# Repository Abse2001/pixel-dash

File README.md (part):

# Pixel Dash

## Accepted populated handheld

The populated AM3354 handheld connects **37 of 50 DDR links** on drilled CAM. A3, A5 and A6 now fit the command placement window together. A joint CPU breakout also shortened WEn. Both complete data bytes, all 44 byte vias and both clock conductors match the locked geometry. The 36-link board remains available at 618d9c6. Fabrication remains on hold. [Full board, top copper](previews/accepted-handheld.png) · [Accepted board and electrical checks](production/accepted) · [Earlier A3/A5/A6 breakout](https://github.com/Abse2001/pixel-dash/tree/82bd23d/studies/paired-command-breakout/return-preserved)

LCD_D1 and LCD_D2 have continuous full-width adjacent ground from their SYSBOOT resistors to the panel outside the plated launches. LCD_D1 shortened from 89.121 to 86.448 mm with nine transitions instead of ten. LCD_D2 shortened from 93.848 to 93.075 mm and retains twelve transitions. Both CPU strap taps remain open. The export has 23 remaining raster ground-coverage findings. [Full-width raster check](production/accepted/raster-reference.txt) · [Physical endpoints](production/accepted/drilled-cam.txt)

Drilled CAM verifies the touch interrupt from AM3354 V14 to R_TOUCH_IRQ pin 1 and verifies pin 2 reaches the 3.3 V DCDC4 rail. Its CPU-side via clears the reference copper under LCD_D9. This closes one of the 39 previously split board nets. Touch SDA and SCL remain open. [Whole-board CAM report](production/accepted/drilled-cam.txt)

The SYSBOOT resistors now reach 16/16 panel data pins on drilled CAM. The new resistor-to-panel connections are bits 4, 5, 6 and 7. The CPU straps physically resolve to `01000?00???????1` (bits 15 through 0). The eight question marks identify unconnected CPU taps. The fitted bias word is 0x4017. Both byte lanes, CK/CKn and all prior command geometry match 740abbe. Full-width DDR/MMC0 checks pass, and the new panel conductors have full ground reference on the export. The LCD_D1 and LCD_D2 repairs reduced the original 25 raster reference findings to 23. [Exact physical strap and panel results](production/accepted/drilled-cam.txt) · [Raster reference](production/accepted/raster-reference.txt)

All previously passing command windows remain passing. A3, A5 and A6 measure 38.14850, 37.21347 and 36.67605 mm inside the 36.14999–38.68999 mm window. A9 shortened from 39.65733 to 38.60715 mm with its RAM-side via retained and the CPU-side transition moved. Its two L1–L4 transitions have 2.84 mm total contacted depth. Modeled arrival is 241.469 ps, or +4.999 ps to mean CK, with 0.08284 mm to the length ceiling. WEn shortened from 40.50792 to 38.66645 mm, leaving 0.02354 mm to the placement ceiling. It now has six transitions and 5.30 mm total contacted depth. The additional inner-layer routing increases modeled flight from 270.856 to 287.897 ps. The nominal first-arrival setup/hold requirement changes from 488.300/311.904 to 505.341/294.863 ps. The route preserves the L3 feed to the RAM supply via and all 20 selected byte return-path measurements. Two connected signals still miss the placement window. BA1 is 9.82286 mm long and CKE is 12.04368 mm short. The setup and hold calculations still need actual source launch and receiver margins. Thirteen signals remain open. [Per-net timing and spans](production/accepted/command-timing.csv) · [Physical open nets](production/accepted/ddr-power-lands.txt)

The separate 38-link study connects A0 while retaining the A9 and WEn placement passes and both locked data bytes. A0 is 51.05487 mm, 12.36488 mm above the placement ceiling. Drilled CAM verifies the extra connection. The study also records the A11/A14 and shorter A0/A7 corridor trials and the CKE and boot launch screens. [Study board, CAM and timing](https://github.com/Abse2001/pixel-dash/tree/b65d4f5/studies/a0-a9-paired)

The 37-link board has 78 signal transitions that change adjacent reference between L2 ground and L3 DDR supply. The longest geometric transfer is on D1 at (−59.455, 15.245) mm. The two vias of C_DDR40 are 9.4851 and 8.7965 mm away. The supply leg includes a staggered transition. Full-width copper coverage alone cannot establish the impedance of this loop. [Reference transfers](production/accepted/reference-transitions.csv)

The drilled copper also changes the distance a return can travel around slots. A 25 µm grid search on the accepted Gerbers finds a continuous L2 ground path of 10.3275 mm and an L3 supply path of 9.1970 mm from the D1 launch at (−59.455, 15.245) mm to the annuli of C_DDR40. An isolated central-bypass study shortens the corresponding paths to 4.7000 and 3.9039 mm. These are lengths of explicit paths in the connected copper. Return current spreads over the planes, and its distribution and transfer impedance remain open. For five selected byte signals, 18 of 20 legs have a path outside the launch region. Two land-side stubs terminate inside it. Run `python checks/measure-return-plane-path.py dist/index.circuit.json engineering.zip DDR_D1 DDR_D14 DDR_D9 DDR_D12 DDR_DQS0`. [Accepted path measurements](production/accepted/plane-paths.csv) · [Central-bypass layout and CAM](https://github.com/Abse2001/pixel-dash/tree/1a3a72e/studies/central-ddr-return) · [A11 escape and A14 restoration study](https://github.com/Abse2001/pixel-dash/tree/c827d16/studies/a11-escape)

For DDR3L-800, Micron's AC135/DC90 input requirements depend on both the command slew and the differential clock slew at the receiver. At 2.0 V/ns command and 1.0 V/ns clock, Table 62 adds 108 ps setup and 95 ps hold, the largest tabulated additions. Table 64 also requires 213 ps continuously beyond the AC threshold for that command slew. The report applies three tabulated slew pairs to each connected synchronous command and gives the required CPU valid interval. Measured or simulated edge shapes at both die loads, clock jitter and source launch timing are still required for margin. Run `python checks/command-receiver-corners.py production/accepted/command-timing.csv`. [Per-signal slew screens](production/accepted/receiver-slew.csv) · [Micron Tables 60–64](https://media.digikey.com/pdf/Data%20Sheets/Micron%20Technology%20Inc%20PDFs/MT41K_DDR3L_4Gb_Rev.Q_Dec2017_DS.pdf#page=102)

At DDR3L-800, a reflected-edge screen across the 13 routed synchronous commands gives a common source capture-phase window of 633.825–2031.463 ps at IOCTRL 0x273 and 687.219–2015.253 ps at reset IOCTRL 0x000. BA1 limits setup and BA0 limits hold in both scenarios. Phase is measured from one source command transition to the rising capture edge, assuming the next command transition occurs 2500 ps later. Each bound includes the worst of 16 terminal-load combinations, both edge polarities, and the maximum Table 62 setup and hold additions (108 and 95 ps) conditional on the input slews lying within the tabulated range. These are source timing requirements. Actual launch phase, slew, PVT, clock jitter, simultaneous switching and the two die responses still require qualification. Reproduce either report with `checks/command-source-echo.py` and `--launch-window --ioctrl 0x273` or `--launch-window --ioctrl 0`. [0x273 per-net bounds](production/accepted/capture-window-0x273.csv) · [Reset per-net bounds](production/accepted/capture-window-0.csv)

The modeled edge slopes limit how the capture-window results can be used. At IOCTRL 0x273 the differential clock is 5.385–6.740 V/ns and the nominal command setup slope is 2.355–3.244 V/ns. All 416 modeled pin/load/polarity cases fall outside Micron Table 62's 1–4 V/ns clock and 0.4–2 V/ns command grid for setup. At reset IOCTRL 0, 208 of 416 cases have both nominal setup slopes in range. All modeled hold edges at both settings cross earlier than the nominal DC-to-VREF secant within that interval and require Micron’s tangent construction. The earlier conditional capture windows cannot establish receiver margin. The edge screen uses the ±180 mV differential thresholds in Table 26, VREF to AC135 for command setup and DC90 to VREF for hold. It uses the reflected single-edge model at the two-die package terminals. Actual source launch, per-die waveforms, impedance and jitter are still open. Reproduce with `checks/command-source-echo.py` using the same circuit, timing CSV and TI archive and the `--slew-screen` option. [0x273 edge results](production/accepted/edge-slew-0x273.csv) · [Reset edge results](production/accepted/edge-slew-0.csv) · [Micron Tables 26, 31 and 62](https://media.digikey.com/pdf/Data%20Sheets/Micron%20Technology%20Inc%20PDFs/MT41K_DDR3L_4Gb_Rev.Q_Dec2017_DS.pdf)

The first-arrival study uses the nominal rising and falling 50 Ω fixture waveforms in TI ZCZ IBIS Model_364. The study assumes the SR10 and I011 command and clock settings in the three DDR_CMDx_IOCTRL registers (low ten bits 0x273), the fitted 49.9 Ω VTP resistor and 1.35 V. These are simulation inputs. Boot firmware/readback still needs to establish what the controller drives. TI TRM Table 9-9 puts A3 and A5 in CMD0, A11 in CMD1 and A14 in CMD2. The model checks all 28 command/control/clock CPU ball names against the IBIS selector.

For each routed synchronous command, the study propagates the incident waveform through its measured board flight and a 50 Ω lossless line into the Micron Table 7 terminal capacitance. It evaluates rising and falling data against a rising differential CK at the 16 vertices of the jointly specified CK, CKn and command load region. Capacitance is the package-terminal value, counted once. The reported intervals refer to the 50% swing of each fixture edge with zero relative source launch offset. They include the AC135 setup and DC90 hold threshold crossings and use the reference-slew receiver requirements. A negative pre-echo headroom marks a crossing beyond the first incident wave's causal range. The result excludes source/package discontinuities, reflections from prior cycles, bit-pattern coupling, slew derating, AC dwell and PVT/jitter. It cannot establish either die's setup or hold margin. Reproduce with `python checks/command-first-arrival.py dist/index.circuit.json production/accepted/command-timing.csv sprm552c.zip` using TI's original ZIP. [Per-command first arrivals](production/accepted/first-arrival.csv) · [TI ZCZ IBIS archive](https://www.ti.com/lit/zip/SPRM552) · [TI AM335x TRM, §9.2.5](https://www.ti.com/lit/pdf/spruh73) · [Micron TwinDie Table 7](https://datasheet.lcsc.com/datasheet/pdf/1a552aaada9c9cb5685b5fb937531c2e.pdf)

The BA0 and CKE control study includes repeated source and capacitive-load reflections. It fits a time-dependent linear source reflection coefficient to the two complementary TI 50 Ω V/T fixture waveforms on their supplied time axes. CK and CKn propagate separately to the differential crossing. At DDR3L-800, the nominal 0x273 case requires up to 426.667 ps setup and 373.537 ps hold for BA0, and 432.274 ps setup and 367.930 ps hold for CKE at reference slew. Across the 32 sampled cases per net, the largest change in setup from including echoes is 0.013 ps for BA0 and 0.004 ps for CKE. Changing the driver assumption has a much larger effect.

TI TRM Table 9-9 maps BA0 to CMD0 pin 2, CK/CKn to CMD0 pins 4/5, and CKE to CMD2 pin 0. The command IOCTRL registers reset to zero. Under this setting the tables specify the fastest slew and 1.6 × Rext, represented here by nominal Model_370. That sensitivity case requires up to 480.236/389.747 ps setup/hold for BA0 and 485.668/384.140 ps for CKE. Boot firmware or register readback must establish the actual values at initialization. Micron Table 7 explicitly includes BA0 and CKE in the package-terminal load limits. The synchronous CKE screen covers power-down entry/exit and self-refresh entry. Self-refresh exit has separate asynchronous requirements. Both simulations assume an isolated edge, a 50 Ω lossless line, zero package-delay imbalance, nominal IBIS waveforms and reference slew. Actual controller launch, package topology, coupling, jitter, voltage/temperature corners and operating-mode sequencing remain open. Run `python checks/command-source-echo.py dist/index.circuit.json production/accepted/command-timing.csv sprm552c.zip --ioctrl 0x273` and repeat with `--ioctrl 0`. [0x273 corner results](production/accepted/source-echo.csv) · [Reset-setting sensitivity](production/accepted/source-echo-reset.csv) · [TI AM335x TRM](https://www.ti.com/lit/ug/spruh73q/spruh73q.pdf)

At the modeled receiver, all isolated BA0, CKE and WEn edges remain beyond the Micron AC135 input threshold through the simulation end. Across 96 load/polarity cases per drive setting the shortest observed continuous dwell is 1,466.596 ps at 0x273 and 1,348.351 ps at 0x000. Micron Table 64 requires up to 213 ps at DDR3L-800. These are lower bounds on isolated-edge dwell. Successive commands, prior reflections and actual launch still govern receiver margin. Reproduce with the source-echo command above and `--dwell`. [0x273 dwell](production/accepted/receiver-dwell.csv) · [0x000 dwell](production/accepted/receiver-dwell-reset.csv) · [Micron Table 64](https://media.digikey.com/pdf/Data%20Sheets/Micron%20Technology%20Inc%20PDFs/MT41K_DDR3L_4Gb_Rev.Q_Dec2017_DS.pdf#page=104)

WEn is CMD0 pin 1. Its reflected-edge calculation over 32 load and polarity cases requires source setup/hold of 505.341/294.863 ps at IOCTRL 0x273 and 558.735/311.073 ps at IOCTRL 0x000. At a 2,500 ps period with one command change per cycle, the capture edge would need to follow the source change by 505.341–2,205.137 ps or 558.735–2,188.927 ps respectively, before slew derating, launch variation, coupling and jitter. These intervals express source requirements. TI datasheet Table 7-58 specifies DDR clock period and supplies no pin-level command launch extrema. [TI AM335x datasheet, §7.7.2.3.1](https://www.ti.com/lit/ds/symlink/am3354.pdf)

TI TRM §7.3.6 identifies the PHY registers as write-only owing to a silicon bug. Record the executed SPL writes for CMD0/1/2 slave ratios at 0x44E1201C, 0x44E12050 and 0x44E12084, and clock inversion at 0x44E1202C, 0x44E12060 and 0x44E12094. The ratio unit is one clock period divided by 256 (9.766 ps at 400 MHz). Table 7-260 and the slave-ratio field figure give differing reset values. Capture the programmed values and clock period before interpreting a ratio. Timing closure also needs characterized or measured command-to-CK launch extrema for the operating configuration. [TI AM335x TRM, Tables 7-260, 7-261 and 7-263](https://www.ti.com/lit/ug/spruh73q/spruh73q.pdf)

Read CONTROL_STATUS at 0x44E10040 after a power-on reset with the panel attached and again with it disconnected. The PWRONRSTn rising edge latches SYSBOOT. A warm reset retains the prior sample. Validate the saved register word with `python checks/check-sysboot.py dist/index.circuit.json --control-status VALUE`. The decoder combines register bits 23:16 and 7:0 into the sixteen strap bits and compares them to the fitted 0x4017 intent. A physical cold-boot capture is pending. [TI TRM Table 9-14 and §26.1.5.2](https://www.ti.com/lit/ug/spruh73q/spruh73q.pdf)

For cold bring-up, capture the three command IOCTRL registers, VTP_CTRL and DDR_CKE_CTRL before the first external memory access. TI TRM Table 9-63 gives VTP_CTRL bits 6 and 5 as dynamic compensation enable and training complete. Table 9-86 gives DDR_CKE_CTRL bit 0 as the gate on the PHY’s CKE output. Its reset value holds external CKE low, which prevents the memory from registering commands. The zero-IOCTRL sensitivity calculation assumes a calibrated driver operating after the gate opens. The power-on reset state itself cannot establish a receiver timing margin.

The fitted TwinDie datasheet delegates initialization to the 4 Gb monolithic device. Verify stable power with RESET# low for at least 200 µs, CKE low for at least 10 ns before RESET# rises, and CKE low for the following 500 µs minus one clock. Before the first registered CKE high, verify valid CK for at least 10 ns and at least five clocks, plus ODT low for the required setup. At DDR3L-800 five clocks take 12.5 ns. RESET# remains physically open on the accepted board. Capture these signals on the first article alongside the supply ramp and retain the MMC0 cold-boot results with the panel attached and disconnected. [TI TRM Tables 9-63 and 9-86](https://www.ti.com/lit/ug/spruh73q/spruh73q.pdf) · [Micron DDR3L initialization](https://media.digikey.com/pdf/Data%20Sheets/Micron%20Technology%20Inc%20PDFs/MT41K_DDR3L_4Gb_Rev.Q_Dec2017_DS.pdf)

Run `bun run build` to materialize the exact qualified circuit at `dist/index.circuit.json`. To screen a reroute, run `bun run check:bytes path/to/candidate.circuit.json` with Python 3 and Shapely 2 installed. Both complete lanes must pass on the same populated candidate. Rerun drilled endpoint and short checks, full-width references, copper and via-edge clearance, drill spacing and supply connectivity on its own export before updating the pinned board. Placement ceilings and modeled flight are project screens. Hardware timing signoff remains open.

To repeat the populated DDR reference check, pass the same circuit and Gerber export to the checker. The thirteen open names must match exactly. Omit the open list for the complete 50-link gate.

```sh
python checks/audit-ddr-reference-planes.py dist/index.circuit.json --gerbers engineering.zip --full-width --study-open DDR_A0 DDR_A1 DDR_A10 DDR_A11 DDR_A12 DDR_A13 DDR_A2 DDR_A4 DDR_CASn DDR_CSn0 DDR_ODT DDR_RASn DDR_RESETn
```

The gate rejected the 45-link powered board for missing D1, D10 and D11. It also rejected the fully connected raster fallback on data and mask timing in both lanes. The accepted board has zero 0.102 mm copper, 0.1524 mm via-edge, drill-spacing or routed DDR reference findings. Thirty-nine whole-board nets still have disconnected copper. [All 22 timing results](production/accepted/byte-timing.csv) · [Drilled CAM](production/accepted/drilled-cam.txt) · [Full-width reference](production/accepted/ddr-reference.txt)

BA0 increased from 35.53782 to 36.26684 mm inside the 36.14999–38.68999 mm placement window. It remains on L1 with zero vias. Estimated flight is 209.223 ps, or −27.247 ps relative to mean CK, previously −31.452 ps. All 22 byte routes and both clock routes retain their fingerprints. Drilled CAM joins N5/P5 to DCDC4, all seven CPU DDR lands to the switched output, all eighteen DRAM supply lands to the DCDC3 inductor output, all 21 DRAM returns to ground, and both terminals of all 40 DDR capacitors to their intended domains. This proves copper continuity. Hot-load transient and receiver timing signoff remain open. MMC0 DAT3 and card detect now avoid the raster strap relief. DAT2 crosses it on L1, with a 0.5 mm return-via distance at each transition. The export has zero full-width MMC0 reference findings and retains all seven card signals and sequenced card power. [MMC0 return check](production/accepted/mmc0-reference.txt) [Power by land](production/accepted/ddr-power-lands.txt) · [Command and clock timing](production/accepted/command-timing.csv)

The command timing CSV gives the required valid interval at the AM3354 balls for the reference-slew DDR3L-800 screen. For board flight difference Δ = signal arrival − mean CK arrival, the required source setup is 365 + Δ ps and hold is 285 − Δ ps. BA0 requires 337.753 ps setup and 312.247 ps hold. The fitted TwinDie package has two command/clock loads. Controller launch limits, package loading, slew derating, clock jitter and stack tolerances are still needed for receiver margin. RESETn needs a sequencing check. Recompute with `python checks/measure-command-timing.py dist/index.circuit.json <prior-circuit.json>`. [Micron x8 device timing, Tables 60–64](https://media.digikey.com/pdf/Data%20Sheets/Micron%20Technology%20Inc%20PDFs/MT41K_DDR3L_4Gb_Rev.Q_Dec2017_DS.pdf#page=102) · [AM3354 DDR3 clock and PCB rules](https://www.ti.com/lit/ds/symlink/am3354.pdf)

At the current package coordinates, an in-memory comparison changes the 42 through vias inside the CPU or DRAM body to 18 mil lands and 10 mil holes. It produces 52 via-edge clearance findings and two drill-spacing findings. The blind and buried vias retain their actual drill spans in this comparison. TI Table 7-62 note 5 describes the 18 mil land for the minimum-layer-count via-channel escape. Qualification of the installed four-layer HDI launches remains open. [Escape measurements](production/accepted/escape-lands.txt)

The reference copper fills the obsolete antipads of the two removed VREFCA bypass vias. Relative to the accepted MMC0 board the L2 ground plane regains 0.66515 mm² and L3 DDR supply regains 0.66893 mm². Full-width checks on the 37 routed DDR signals and seven MMC0 signals remain clean. The conservative whole DDR envelope still has 57 findings. Outside nominal via antipads, L2 ground coverage misses 12.38295 mm² and L3 DDR supply coverage misses 91.82907 mm². Existing inner traces and the neighboring ground pour account for most of the residual. The separate raster check reproduces the fallback’s 25 findings on 14 routed signals. [Whole-envelope CAM](production/accepted/ddr-envelope.txt)

An earlier 37-link study added A10 to the 36-link fallback. A7, A10 and A14 fit the nominal command length window together. A6 reaches both balls but exceeds its ceiling by 11.45448 mm, so the accepted build retains the shorter A6. The drilled study has 13 DDR opens and both bytes pass unchanged. [Study PCB, clock-relative timing and drilled endpoints](https://github.com/Abse2001/pixel-dash/tree/8df6773/studies/accepted-a10-corridor/37-links)

To verify an intermediate export, pass its native circuit, its Gerber/Excellon ZIP and the independently expected open control names to `python checks/audit-cam-connectivity.py BOARD ZIP --ddr-checkpoint OPEN_CONTROL ...`. This checks exactly which physical DDR pairs connect, rejects aliases and shorts, requires all data, masks, strobes and clocks, and verifies DDR power lands and MMC0. The normal whole-board invocation still requires all 50 DDR pairs. Run the separate timing and reference checks on the same circuit and export.

## Separate powered routing studies

Powered checkpoint `7ac53c5` connects LCD data-enable from U1.R6 to J_LCD pin 9 with a continuous full-width reference. Drilled CAM verifies 12/29 CPU-to-panel signals, 16/16 panel-side strap taps, seven CPU strap states and 45/50 DDR links. Twenty-eight mapped board nets remain split. DE's nominal flight is 0.7635 ns later than PCLK. Panel receiver timing remains open. All 71 local DDR returns, sequenced MMC0, the DDR timing CSV, copper, via-edge and drill checks retain their prior results. [Full PCB](https://github.com/Abse2001/pixel-dash/blob/7ac53c5/studies/powered-cpu-io/powered-panel-taps.png) · [Drilled CAM](https://github.com/Abse2001/pixel-dash/blob/7ac53c5/studies/powered-cpu-io/panel-DE-cam.txt) · [Raster flight](https://github.com/Abse2001/pixel-dash/blob/7ac53c5/studies/powered-cpu-io/panel-clock-flight.csv)

West trial `a466259` restores D0 alongside D5, D7, DQM0 and both shortened strobes. The six fit the 20.6001 mm placement cap, TI matching limits and the nominal ±3.6633 ps board-skew screen together. The new strobe mismatch is 0.0260 mm against 0.127 mm. Drilled CAM verifies 40/50 links. All routed traces and the DDR envelope pass reference checks. The separate copper, 6 mil via-edge, drill spacing and nonlocal DDR contact audits report zero findings. Fifteen more command/address paths fit the 30.150–32.690 mm placement window. A3, A6, A11 and CKE still miss it. Five byte-zero DQ paths and the full receiver timing budget remain open. The powered and fully connected fallbacks remain available. Fabrication is on hold. [Per-net pass/fail with targets and residuals](https://github.com/Abse2001/pixel-dash/blob/2e49c6f/studies/powered-ddr3l-offset/short-strobe/west-gate-status.csv) · [D2 physical trial](https://github.com/Abse2001/pixel-dash/tree/study/powered-ddr3l-offset/studies/powered-ddr3l-offset/short-strobe/escape-screen) · [Physical geometry, pin map and receiver assumptions](https://github.com/Abse2001/pixel-dash/tree/a466259/studies/powered-ddr3l-offset/short-strobe) · [Earlier B5 and command trials](https://github.com/Abse2001/pixel-dash/tree/01116f0/studies/powered-ddr3l-offset/rtc-reset)

The four-route west trial preserves the 20.600104 mm cap with both byte lanes installed. Local D12/D14 changes reduced the 0.102 mm copper findings from 25 to 24, the 6 mil via-edge findings from nine to eight and the full-width return findings from seven to six. Drilled CAM still finds shorts on the trial. The separate clean CKE study shortens CKE from 34.9054 to 34.8683 mm with 40 distinct links and all 71 local returns. Its 32.690 mm upper target and receiver timing remain open. [Four-route mapping, full circuit and physical findings](https://github.com/Abse2001/pixel-dash/tree/dd87640/studies/powered-ddr3l-offset/short-strobe/four-route-recheck) · [CKE timing and drilled CAM](https://github.com/Abse2001/pixel-dash/tree/4dfb0ab/studies/powered-ddr3l-offset/short-strobe/cke)

## Separate 50-link routing study

The complete candidate at 4b3d1c5 connects the handheld IRQ pull-up, keeps the 50 DDR routes and their vias identical to a4a71e2 and reduces the whole-board split-net count from 35 to 34. Drilled CAM explicitly verifies J3/VTP, RAM ZQ, the CPU and RAM VREF networks, divider rails, local bypass returns and their mutual isolation. [Complete candidate and physical land groups](https://github.com/Abse2001/pixel-dash/blob/4b3d1c5/checks/current-touch-irq-cam.txt)

The powered board at 408d38c connects touch IRQ, the panel-side D3 and D4 strap taps, and the complete U1.T4 to LCD D7 path. Exact CAM shows 45 distinct DDR signals, 13/16 panel taps, 8/29 CPU-to-panel signals, seven physically resolved CPU straps, and 34 split mapped nets. Timing is unchanged from d8461d7. N5/P5, VTP, ground and full-width return checks pass. The original 45-link d8461d7, 50-link 4b3d1c5 and rotated b0317c2 stay separate. [Full powered PCB and CAM](https://github.com/Abse2001/pixel-dash/tree/408d38c/studies/powered-cpu-io) · [Byte-zero simultaneous landing and installed-peer bounds](https://github.com/Abse2001/pixel-dash/tree/study/byte0-two-transition/studies/byte0-two-transition)

The rotated study at b0317c2 connects U1.V14 to the touch IRQ pull-up and preserves all mapped handheld ground connections. Fifty mapped whole-board nets remain split. The powered 45-link baseline stays at d8461d7. The 26-link study passes relative matching for its eight routed data lines, but all four routed upper-byte data lines and both upper strobes exceed the 14.200 mm project length gate. No in-byte remap alone can raise it beyond 14.99986 mm at this placement. [Full PCB snapshot and CAM](https://github.com/Abse2001/pixel-dash/tree/b0317c2/studies/quarter-turn/touch-irq) · [Per-net gate and remap bounds](https://github.com/Abse2001/pixel-dash/blob/b0317c2/studies/quarter-turn/d1-restored/remap-length-bound.csv)

The rotated study at b5e1c20 physically connects B5 (RTC reset) to PMIC PGOOD_BU, C5 to wake, and B4 to the 1.8 V D7/DCDC6 rail. B4 remains isolated from D6/DCDC5. All mapped ground lands and barrels join the UART ground probe, including the two nearby bypass returns. Twenty-six DDR signals, eight physical SYSBOOT straps, 22 CPU DDR bypasses, 14 DRAM bypasses and 71 local reference terminals pass their connectivity checks. The export still has 51 split mapped nets. [Full PCB snapshot, drilled CAM and timing](https://github.com/Abse2001/pixel-dash/tree/b5e1c20/studies/quarter-turn/rtc-reset)

The rotated populated study at 5494ca2 now connects 26 DDR signals. D1, D2, D3, D4, D10, D11, D12 and D14 pass present-peer and strobe matching plus the reference-stack delay screen together. All 71 local return terminals and both CPU supply feeds pass. Twenty-four DDR signals and whole-board closure remain open. [Full PCB snapshot, per-net limits and physical CAM](https://github.com/Abse2001/pixel-dash/tree/5494ca2/studies/quarter-turn/d1-restored)

The rotated RAM study at 9c71554 connects 25 distinct DDR signals on the powered handheld. D2/D3/D4 and D10/D11/D12/D14 pass their local TI length and modeled skew screens together. A10, A14, BA2 and CK/CKn are physically connected, with command timing still open. SYSBOOT0 reaches the CPU, its high strap and panel. All 71 local DDR return terminals pass. The powered 45-link baseline remains separate. [Full-board copper, per-net timing and drilled CAM](https://github.com/Abse2001/pixel-dash/tree/9c71554/studies/quarter-turn/ba2-breakout)

A separate 90° RAM placement at f7b27e7 routes D2, D3 and D4 together with a matched DQS0 pair. All five use two full-depth transitions, pass drilled CAM, and retain the local power and return paths. Worst modeled data skew is +1.7561 ps against ±3.6633 ps. This five-link study reserves startup space at SYSBOOT0. The unchanged RAM orientation leaves the entire SYSBOOT0 pad inside the required margin even if all DDR routes are lifted. [Timing, geometry, assembled study and drilled CAM](https://github.com/Abse2001/pixel-dash/tree/f7b27e7/studies/quarter-turn/timed-d234) · [Placement measurements](https://github.com/Abse2001/pixel-dash/tree/fcbf70b/studies/quarter-turn)

The powered board at d8461d7 also connects SYSBOOT7 and SYSBOOT12 to their bias resistors. Seven straps have verified physical states. The DDR bus remains at 45/50, with its full timing CSV and reference checks preserved. [Current powered board and drilled strap results](https://github.com/Abse2001/pixel-dash/tree/d8461d7/studies/powered-cpu-io)

The powered I/O checkpoint at 8c7bccf closes physical SYSBOOT10, panel D10, backlight PWM and amplifier logic bias. It retains the 45 DDR links, their complete timing CSV and the two power feeds. CAM reports 36 split whole-board nets. On the unchanged e5fd49f copper, the independent two-transition screen finds all nine D2/D3/D4 pin assignments disconnected within 20.4313 mm with their neighbors fixed. Releasing D0 or A1 restores individual reachability. [Powered I/O checkpoint and CAM](https://github.com/Abse2001/pixel-dash/tree/8c7bccf/studies/powered-cpu-io) · [Length-bounded topology screen](https://github.com/Abse2001/pixel-dash/tree/aa53c0e/studies/byte0-two-transition)

The powered baseline at 4fd6b86 shortens D5 to 25.7789 mm and retains its 45 distinct DDR links. On the alternative D15-passing branch, e5fd49f also removes two D7 transitions. D7 improves from +38.5076 to +16.5431 ps against the ±3.6633 ps model screen. Neither byte is complete. [Powered baseline timing](https://github.com/Abse2001/pixel-dash/blob/4fd6b86/studies/powered-byte1/d5-timing.csv) · [Alternative D5/D7 report and CAM](https://github.com/Abse2001/pixel-dash/tree/e5fd49f/studies/powered-byte1)

The native build of the powered 45-link board is verified at fc8c13c. A separate crossing trial at 354eaf8 brings D15 to 22.6549 mm with −1.8131 ps worst signed skew against the ±3.6633 ps model gate. It preserves the physical supplies and all 45 links, but moving the intermediate D3 bridge increases its skew to +54.1593 ps. Both byte lanes still have open signals. [Passing D15, D3 regression and exact CAM results](https://github.com/Abse2001/pixel-dash/tree/354eaf8/studies/powered-byte1)

The powered byte-1 study at 178dd63 has 45/50 distinct DDR connections. D12, D13 and D14 meet their TI strobe matching and model skew gates. D13 has just 0.0977 ps of modeled headroom. D15 is connected and retains full reference coverage, but its +5.4050 ps worst modeled skew exceeds the ±3.6633 ps screen. A10, A14, D1, D10 and D11 still need copper. Both N5/P5 and the VTP resistor return pass drilled CAM. [Timing, exact physical lands and intermediate fallbacks](https://github.com/Abse2001/pixel-dash/tree/178dd63/studies/powered-byte1)

The separate four-route breakout moves the switched DDR feed to make room for N5/P5. It physically connects 21/21 DCDC4 lands and 7/7 switched CPU DDR lands, with D1, D12, A10 and A14 lifted. [Boot-power study and screening results](https://github.com/Abse2001/pixel-dash/tree/ff755ca/studies/boot-ddr-breakout)

The four-layer AM3354 handheld at a4a71e2 retains 50 distinct CPU-to-RAM signals. BA2 shortened from 29.7914 to 28.6872 mm inside its 28.550–31.090 mm project window. Modeled arrival relative to mean CK improved from +10.7705 to +4.4005 ps. All DDR vias and the other 49 routes are unchanged. D11 and D15 now have continuous exported raster reference, including the strap traces. Independent CAM passes the common DDR envelope and full-width DDR, MMC0 and raster checks. Data-byte timing, command receiver signoff, N5/P5 power, physical straps and whole-board release remain open. [Full PCB snapshot](https://github.com/Abse2001/pixel-dash/blob/a4a71e2/previews/handheld.png) · [Per-net timing](https://github.com/Abse2001/pixel-dash/blob/a4a71e2/checks/current-ddr-change.csv) · [Physical land report](https://github.com/Abse2001/pixel-dash/blob/a4a71e2/checks/current-raster-taps-cam.txt)

The isolated D12/D1 trial retains all 50 distinct DDR pairs and passes copper, drilling and full-width reference checks. Both shortened signals still miss the TI and model matching targets. On the full board, A10/A14 also bound the N5/P5 escape. With D12/D1 entirely removed, neither supply pad has any exposed copper beyond the DDR margin. [Trial, timing targets and physical lands](https://github.com/Abse2001/pixel-dash/tree/12332c9/studies/d12-d1-breakout)

The separate boot study connects all 21 DCDC4 lands and SYSBOOT12. Its N5 and P5 copper and the V2 strap escape fail the common keepout. Both power pads are wholly inside even the smaller envelope defined by the locked bytes and clock. [Boot study and CAM findings](https://github.com/Abse2001/pixel-dash/tree/8c27acf/studies/complete-boot-escape)

The protected populated board has 36/50 distinct CPU–RAM signals and all 22 original byte routes. A8 measures 36.533 mm in its 36.150–38.690 mm placement window and arrives an estimated 0.107 ps before mean CK. RTC reset, wake, power hold and the isolated DCDC5/DCDC6 core and I/O connections pass drilled CAM. Six of sixteen SYSBOOT bits reach the CPU. [Protected board and timing](https://github.com/Abse2001/pixel-dash/tree/076b815/studies/clock-first) · [Protected full-board snapshot](https://github.com/Abse2001/pixel-dash/blob/076b815/studies/clock-first/populated-handheld.png)

The populated CPU escape trial connects the driven VREF divider and bypass to J4, J3 to the grounded calibration resistor, and all 21 CPU DCDC4 lands including N5/P5. Eight reset straps reach the CPU. Raster D12 reaches panel pin 15. Panel D3 reaches its strap resistor and still needs CPU ball R4. Twelve of sixteen panel data pins reach the strap pads, with 25 existing raster reference findings. Exported CAM resolves 36/50 distinct DDR pairs. A0 and A10 lost connectivity during clock routing, with identical CPU and DRAM pin assignments at both checkpoints. The 22 byte routes and clock pair retain the e4c906f geometry. Fourteen open DDR links, receiver timing and remaining boot and board-level checks keep fabrication on hold. [Physical evidence](https://github.com/Abse2001/pixel-dash/tree/b5356e7/studies/electrical-closure) · [Full-board PCB](https://github.com/Abse2001/pixel-dash/blob/b5356e7/studies/j4-vref/populated-handheld.png) · [Rejected A7/A10 exchange and exact CAM results](https://github.com/Abse2001/pixel-dash/tree/470c8be/studies/a7-a10-corridor)

## Populated handheld DDR data checkpoint

The tagged populated layout preserves all 22 passing byte 0 and byte 1 routes through 44 plated vias. The handheld Gerbers verify each distinct CPU-to-RAM pair, full-width reference coverage and zero mapped-land shorts. All 236 component courtyards clear after relocating eight passives. The other 28 DDR links remain open on this checkpoint. [Saved populated circuit and checks](https://github.com/Abse2001/pixel-dash/tree/pixel-dash-populated-ddr-locked/studies/data-bytes) · [Preserved breakout](https://github.com/Abse2001/pixel-dash/tree/pixel-dash-ddr-bytes-verified-2dc2af8)

## DDR timing study

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
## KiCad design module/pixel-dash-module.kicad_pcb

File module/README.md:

# AM3354 + DDR3L compute module

A 50 x 36 mm, 6-layer, 1.0 mm board that carries only what needs six layers: the AM3354BZCZD80 (U1), the
MT41K512M16VRP DDR3L (U_DDR), the DDR3 routing between them, their decoupling, the DDR reference/calibration
parts and the 24 MHz crystal. Everything else (power chip, boot straps, SD, USB, display, buttons, debug) lives on
the handheld and reaches the module through two Hirose DF40C-100DS-0.4V connectors (J1, J2, bottom side; the
handheld carries DF40C-100DP, LCSC C531031).

| Layer | Use |
|---|---|
| L1 top | DDR + handheld signals, both BGAs, crystal |
| L2 | ground |
| L3 | VDDS_DDR (west, the processor's north and south rows and its core-ball interior, with the DDR_VREF link embedded), 3V3 (the processor's middle rows and the east edge) |
| L4 | VDD_CORE, VDD_MPU, part of 1V8, DDR_VREF (between the chips), the 23 handheld signals whose balls sit inside the DDR fan-out |
| L5 | ground |
| L6 bottom | DDR + handheld signals, decoupling, connectors |

Through vias only, no blind or buried vias: 0.1 mm holes in 0.3 mm pads, via-in-pad throughout. The 0.1 mm hole keeps every hole wall at least 0.2 mm from other copper on the outer layers and 0.225 mm on the planes (JLCPCB: 0.2 mm); it needs a board of 1 mm or less with ENIG.

## What the handheld has to provide

Rails, through the connector pins listed in `fab/pinmap.csv`:

| Rail | Pins | Notes |
|---|---|---|
| VDD_CORE 1.1 V | J2, 4 | |
| VDD_MPU 1.1-1.26 V | J2, 6 | |
| VDDS_DDR 1.35 V (1.5 V) | J1, 4 | feeds the processor's DDR I/O, the memory and the VREF divider |
| VDD_3V3 | J1, 3 | VDDSHVx and USB 3.3 V |
| VDD_1V8 | J1, 2 | VDDS, PLL, oscillator, USB and ADC 1.8 V balls (ADC unused: VREFP on 1.8 V, VREFN on ground) |
| VDDS_RTC 1.8 V | J2, 1 | RTC domain; the internal RTC regulator is enabled (RTC_KALDO_ENn grounded, 1 uF on CAP_VDD_RTC) |
| GND | 55 | |

Follow the AM335x power-up sequence on the handheld (SPRS717L section 6.1) and drive `PWRONRSTn` and
`RTC_PWRONRSTn` from it. `LCD_D0..LCD_D15` are the SYSBOOT pins: the boot-mode resistors go on the handheld.
I2C0 needs its pull-ups there too. 75 signals are wired, 50 connector pins are spare.

## Files

- `fab/module-gerbers.zip` (and `fab/gerbers/`), `fab/bom.csv`, `fab/cpl.csv`: what a fab/assembly quote needs.
- `fab/pinmap.csv`: every connector pin with its net, processor ball and position.
- `fab/views/*.png`: one picture per copper layer.
- `dist/module.circuit.json`: the board as tscircuit circuit JSON.

Ordering notes (JLCPCB): 6 layers, 1.0 mm, ENIG, minimum hole 0.1 mm / via pad 0.3 mm, trace/space 0.1 mm,
vias epoxy-filled and capped (via-in-pad), both sides assembled. Outer prepreg (L1-L2, L5-L6) 1080 or 3313, not 7628:
that puts the 0.102 mm outer traces at 56-63 ohm (TI: 50-75); 7628 would give 89 ohm (`si/zo_results.txt`).
Bring-up: set the processor's DDR command/address/clock drive to 40 ohm or weaker (`si/README.md`).

## Rebuilding

`module/make.sh` runs the whole chain and ends with the whole-board check:

1. `plan.ts` loads the routed, verified DDR block (`ddr-route/out/module9`) and places every other part and via.
2. `route.sh` (`route-signals.ts`) routes the handheld signals to free connector pins.
3. `TOPUP=1 plan.ts` adds the bypass capacitors that had to wait for those routes.
4. `planes.ts` builds the inner-layer copper; `build.tsx` renders `dist/module.circuit.json`.
5. `check.ts` checks the rendered board: pad positions, clearances, shorts, every net one piece.
6. `export.ts` and `layers.py` write `fab/`.

The DDR block itself is produced and checked in `ddr-route` (`route-staged.ts`, two-layer mode, seed 5, `exactViasByBus` = 2 for
both bytes and address/control/clock, keepouts `runs/mod8.keepouts.json`; then `clean-wiggles.ts`, `verify.ts`,
`spec-check.ts` with `THROUGH=1`, `selfgap.ts`).

## Checks behind this build

- DDR block (`ddr-route/out/module9`): connectivity/clearance, TI SPRS717L Tables 7-68/7-69 lengths and skews,
  spacing allowance (also with the module's other traces as neighbours), same-net gaps: all pass.
- Whole board (`check.ts`): 141/141 nets one piece, no shorts, minimum clearance 0.100 mm, drill walls >= 0.30 mm apart,
  hole wall to other copper >= 0.200 mm (outer) / 0.225 mm (planes), through vias only.
- Independent audit from the Gerbers and the drill file (own parser): 0 shorts, 0 opens, every pour present,
  mask/paste on all 794 pads, vias tented, bypass counts and distances per Table 7-64/7-65 met
  (processor 20 x 100 nF within 306 mil of 400, memory 12 within 61 mil of 150, 2 x 10 uF bulk each).
- Plane voltage drop (`irdrop3d.py`: all four inner layers joined at the vias, 17.5 um copper, plated 0.1 mm barrels;
  `power-results.txt`): VDD_CORE 2.5 mV at 0.4 A, VDD_MPU 5.1 mV at 1 A, VDDS_DDR 7.4 mV at 0.6 A, VDD_1V8 14 mV at
  0.2 A, VDD_3V3 15 mV at 0.25 A (all under 1 % of the rail).
- DDR bypass connection (`hs_loop.py`): all 20 processor HS capacitors have their VDDS_DDR via in VDDS_DDR copper on
  layer 3 (L3 carries VDDS_DDR in the processor's north/south rows and core-ball interior for this); plane spreading
  inductance 0.69-2.4 nH each, 72 pH for the twenty in parallel including their vias.
- DDR: every net has exactly two vias and runs on the outer layers only, so the via length is the same for every
  net of every matched group, and the in-plane lengths and skews meet TI's tables.
- No VTT termination on address/control/clock: TI's Figure 7-48 topology for one memory device. Coupled-line
  simulation of the worst net with its neighbours, losses, vias and packages (`si/`): passes the DDR3L levels with
  the drive at 40 ohm or weaker on every usable prepreg. No IBIS models; measure on the first boards.
- D3 and D7 are swapped at the memory (within byte 0, deliberate, DQ0 untouched).
- Via-in-pad everywhere: every handheld-signal via inside the processor's ball field sits exactly on its ball centre
  or >= 0.45 mm from every ball centre; no via pad overlaps a pad of another net (bypass-capacitor vias keep
  >= 0.104 mm to the ball pads). Order epoxy-filled and capped vias.
- USB0 D+/D- run side by side (11 mm, equal length) but not as an impedance-controlled pair.
- 1.8 V PLL/oscillator/USB supply balls share the 1.8 V plane without ferrites.
- Connector pin numbers in `fab/pinmap.csv` follow the LCSC footprint (1-50 outer row, 51-100 inner row).
  Lay out the handheld from the X/Y positions, not from pin numbers. The land pattern follows Hirose's drawing
  is the JLCPCB/LCSC footprint of C597931 as imported (rows 3.90 mm outside, 2.50 mm inside; Hirose draws 3.78 / 2.38, the contacts land inside both).
- C_VREF_CPU (0.1 uF on the processor's DDR_VREF) sits 5.9 mm from the J4 ball (TI: "near", no number); closer
  sites are inside the bottom-side DDR fan-out.
- Crystal Y_OSC0: LCSC C362341 (24 MHz, 10 pF, 30 ohm, +/-10/+/-20 ppm, -40..85 C) replaced C439045 (out of stock);
  same land pattern. With the 15 pF capacitors and the short routed traces the load is about 9-10 pF, which suits a
  10 pF crystal (TI Table 6-2: ESR <= 48 ohm, +/-50 ppm total, C1/C2 12-24 pF).
- BOM part numbers and pick-and-place rotations need the usual review in the assembly preview.
  Stock at the time of writing: AM3354BZCZD80 27 pcs, MT41K512M16VRP-107 IT:P 281 pcs (about 70 USD each).

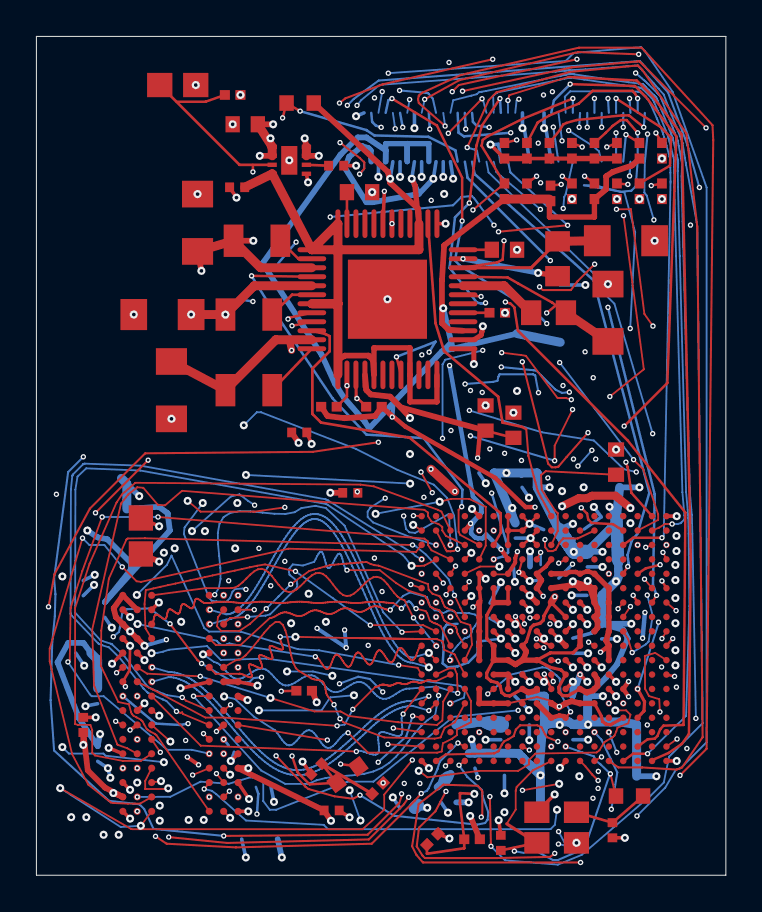
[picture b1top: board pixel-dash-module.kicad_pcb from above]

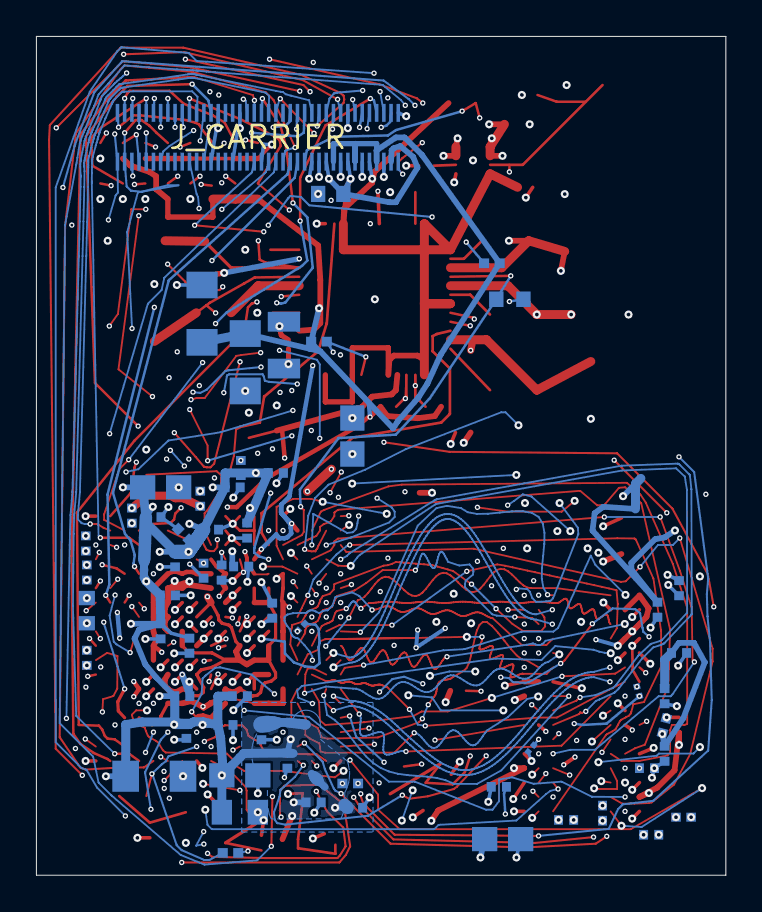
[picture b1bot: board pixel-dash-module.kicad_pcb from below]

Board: 6 copper layers, 38.3 x 46.6 mm, 119 parts (60 on the bottom side), 152 nets.

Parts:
C_CPU_VREF: TMK063ABJ104KP-F
C_DDR1, C_DDR2, C_DDR3, C_DDR4, C_DDR5, C_DDR6, C_DDR7, C_DDR8, C_DDR9, C_DDR10, C_DDR11, C_DDR12, C_DDR13, C_DDR14, C_DDR15, C_DDR16, C_DDR17, C_DDR18, C_DDR19, C_DDR20, C_DDR21, C_DDR22, C_DDR23, C_DDR24, C_DDR25, C_DDR26, C_DDR27, C_DDR28, C_DDR29, C_DDR30, C_DDR31, C_DDR32, C_DDR37, C_DDR38, C_DDR39, C_DDR40: CL05B104KO5NNNC
C_DDR33, C_DDR34: GRM21BC81C226ME44L
C_DDR35, C_DDR36: CL21A226MAQNNNE
C_DDR_SW_BIAS: CL05B104KO5NNNC
C_DDR_SW_CT: 0402B102K500NT
C_DDR_SW_EN: CL21A226MAQNNNE
C_DDR_SW_IN: CL10A106KP8NNNC
C_DDR_SW_LOAD: CL31A476MPHNNNE
C_H1_VREF: TMK063ABJ104KP-F
C_MPU_HF1, C_MPU_HF2, C_MPU_HF3, C_MPU_HF4, C_MPU_HF5: CL05B103KB5NNNC
C_MPU_LOCAL: CL10A106KP8NNNC
C_OSC0_IN, C_OSC0_OUT: 0402CG150F500NT
C_PMIC_CORE: CL31A476MPHNNNE
C_PMIC_DDR: CL31A476MPHNNNE
C_PMIC_INT_LDO: CL10A105KB8NNNC
C_PMIC_IN_BU: CL10A475KO8NNNC
C_PMIC_IO_A: CL31A476MPHNNNE
C_PMIC_IO_B: CL31A476MPHNNNE
C_PMIC_LDO1: CL21A226MAQNNNE
C_PMIC_MPU: CL31A476MPHNNNE
C_PMIC_RTC_CORE: CL31A476MPHNNNE
C_PMIC_RTC_IO: CL31A476MPHNNNE
C_PMIC_SYS_BU: CL10A105KB8NNNC
C_SRAM_CORE: CL05A105KA5NQNC
C_SRAM_CORE_IN: CL10A106KP8NNNC
C_SRAM_MPU: CL05A105KA5NQNC
C_SRAM_MPU_IN: CL10A106KP8NNNC
C_VBB_MPU: CL10A105KB8NNNC
C_VREF_CA: CL05B104KO5NNNC
C_VREF_DQ: CL05B104KO5NNNC
J_CARRIER: DF40C-80DP-0.4V(51)
L_PMIC_CORE: SPM3012T-1R5M
L_PMIC_DDR: SPM3012T-1R5M
L_PMIC_IO: SPM3012T-1R5M
L_PMIC_MPU: SPM3012T-1R5M
L_PMIC_RTC_CORE: LQM21FN100M80L
L_PMIC_RTC_IO: LQM21FN100M80L
R_CPU_VREF_HIGH: 0402WGF1001TCE
R_CPU_VREF_LOW: 0402WGF1001TCE
R_DDR_SW_EN: 0402WGF2200TCE
R_DDR_SW_OUT: 0805W8F470JT5E
R_DDR_VSEL: RT0402BRD0712K1L
R_OSC0_BIAS: RTT021004BTH
R_OSC0_DRIVE: 0603WAF0000T5E
R_PMIC_IRQ: 0402WGF1002TCE
R_PMIC_POR: 0402WGF1002TCE
R_PMIC_SCL: FRC0402J222 TS
R_PMIC_SDA: FRC0402J222 TS
R_PMIC_WAKE: A_0603WAF1003T5E
R_POWER_PB: A_0603WAF1003T5E
R_SYSBOOT0, R_SYSBOOT1, R_SYSBOOT2, R_SYSBOOT3, R_SYSBOOT4, R_SYSBOOT5, R_SYSBOOT6, R_SYSBOOT7, R_SYSBOOT8, R_SYSBOOT9, R_SYSBOOT10, R_SYSBOOT11, R_SYSBOOT12, R_SYSBOOT13, R_SYSBOOT14, R_SYSBOOT15: 0402WGF1002TCE
R_VREF_CA: 0603WAF0000T5E
R_VREF_HIGH: 0402WGF1001TCE
R_VREF_LOW: 0402WGF1001TCE
R_VTP: 0402WGF499JTCE
R_ZQ: RC0201FR-07240RL
U1: AM3354BZCZD80
U_DDR: MT41K512M16VRP-107 IT:P
U_DDR_SWITCH: TPS22975DSGR
U_PMIC: TPS65218D0PHPR
Y_OSC0: S3B24.000000F1210F30

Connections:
AUDIO_PWM_INTERNAL: J_CARRIER.27, U1.A17
CPU_COLD_RESET: R_PMIC_POR.pin1, U1.B15, U_PMIC.PGOOD
CPU_DDR_VREF: C_CPU_VREF.pin1, R_CPU_VREF_HIGH.pin1, R_CPU_VREF_LOW.pin1, U1.J4
CPU_WARM_RESET: U1.A10, U_PMIC.GPIO3
DCDC4_SW_A: L_PMIC_IO.pin1, U_PMIC.L4A
DCDC4_SW_B: L_PMIC_IO.pin2, U_PMIC.L4B
DDR_A0: U1.F3, U_DDR.N3
DDR_A1: U1.H1, U_DDR.P7
DDR_A2: U1.E4, U_DDR.P3
DDR_A3: U1.C3, U_DDR.N2
DDR_A4: U1.C2, U_DDR.P8
DDR_A5: U1.B1, U_DDR.P2
DDR_A6: U1.D5, U_DDR.R8
DDR_A7: U1.E2, U_DDR.R2
DDR_A8: U1.D4, U_DDR.T8
DDR_A9: U1.C1, U_DDR.R3
DDR_A10: U1.F4, U_DDR.L7
DDR_A11: U1.F2, U_DDR.R7
DDR_A12: U1.E3, U_DDR.N7
DDR_A13: U1.H3, U_DDR.T3
DDR_A14: U1.H4, U_DDR.T7
DDR_A15: U1.D3, U_DDR.M7
DDR_BA0: U1.C4, U_DDR.M2
DDR_BA1: U1.E1, U_DDR.N8
DDR_BA2: U1.B3, U_DDR.M3
DDR_CASn: U1.F1, U_DDR.K3
DDR_CK: U1.D2, U_DDR.J7
DDR_CKE: U1.G3, U_DDR.K9
DDR_CKn: U1.D1, U_DDR.K7
DDR_CSn0: U1.H2, U_DDR.L2
DDR_D0: U1.M3, U_DDR.G2
DDR_D1: U1.M4, U_DDR.F7
DDR_D2: U1.N1, U_DDR.H3
DDR_D3: U1.N2, U_DDR.H7
DDR_D4: U1.N3, U_DDR.F2
DDR_D5: U1.N4, U_DDR.H8
DDR_D6: U1.P3, U_DDR.E3
DDR_D7: U1.P4, U_DDR.F8
DDR_D8: U1.J1, U_DDR.A7
DDR_D9: U1.K1, U_DDR.C2
DDR_D10: U1.K2, U_DDR.A3
DDR_D11: U1.K3, U_DDR.C3
DDR_D12: U1.K4, U_DDR.C8
DDR_D13: U1.L3, U_DDR.D7
DDR_D14: U1.L4, U_DDR.B8
DDR_D15: U1.M1, U_DDR.A2
DDR_DQM0: U1.M2, U_DDR.E7
DDR_DQM1: U1.J2, U_DDR.D3
DDR_DQS0: U1.P1, U_DDR.F3
DDR_DQS1: U1.L1, U_DDR.C7
DDR_DQSn0: U1.P2, U_DDR.G3
DDR_DQSn1: U1.L2, U_DDR.B7
DDR_ODT: U1.G1, U_DDR.K1
DDR_RASn: U1.G4, U_DDR.J3
DDR_RESETn: U1.G2, U_DDR.T2
DDR_SWITCH_ENABLE: C_DDR_SW_EN.pin1, R_DDR_SW_EN.pin1, U_DDR_SWITCH.ON, U_PMIC.LS1
DDR_VREF: C_H1_VREF.pin1, C_VREF_DQ.pin1, R_VREF_CA.pin2, R_VREF_HIGH.pin1, R_VREF_LOW.pin1, U_DDR.H1
DDR_VREF_CA: C_VREF_CA.pin1, R_VREF_CA.pin1, U_DDR.M8
DDR_VTP: R_VTP.pin1, U1.J3
DDR_WEn: U1.B2, U_DDR.L3
DDR_ZQ: R_ZQ.pin1, U_DDR.L8
DEBUG_UART0_RX: J_CARRIER.65, U1.E15
DEBUG_UART0_TX: J_CARRIER.66, U1.E16
GND_INTERNAL: C_CPU_VREF.pin2, C_DDR1.pin2, C_DDR2.pin2, C_DDR3.pin2, C_DDR4.pin2, C_DDR5.pin2, C_DDR6.pin2, C_DDR7.pin2, C_DDR8.pin2, C_DDR9.pin2, C_DDR10.pin2, C_DDR11.pin2, C_DDR12.pin2, C_DDR13.pin2, C_DDR14.pin2, C_DDR15.pin2, C_DDR16.pin2, C_DDR17.pin2, C_DDR18.pin2, C_DDR19.pin2, C_DDR20.pin2, C_DDR21.pin2, C_DDR22.pin2, C_DDR23.pin2, C_DDR24.pin2, C_DDR25.pin2, C_DDR26.pin2, C_DDR27.pin2, C_DDR28.pin2, C_DDR29.pin2, C_DDR30.pin2, C_DDR31.pin2, C_DDR32.pin2, C_DDR33.pin2, C_DDR34.pin2, C_DDR35.pin2, C_DDR36.pin2, C_DDR37.pin2, C_DDR38.pin2, C_DDR39.pin2, C_DDR40.pin2, C_DDR_SW_BIAS.pin2, C_DDR_SW_CT.pin2, C_DDR_SW_EN.pin2, C_DDR_SW_IN.pin2, C_DDR_SW_LOAD.pin2, C_H1_VREF.pin2, C_MPU_HF1.pin2, C_MPU_HF2.pin2, C_MPU_HF3.pin2, C_MPU_HF4.pin2, C_MPU_HF5.pin2, C_MPU_LOCAL.pin2, C_OSC0_IN.pin2, C_OSC0_OUT.pin2, C_PMIC_CORE.pin2, C_PMIC_DDR.pin2, C_PMIC_INT_LDO.pin2, C_PMIC_IN_BU.pin2, C_PMIC_IO_A.pin2, C_PMIC_IO_B.pin2, C_PMIC_LDO1.pin2, C_PMIC_MPU.pin2, C_PMIC_RTC_CORE.pin2, C_PMIC_RTC_IO.pin2, C_PMIC_SYS_BU.pin2, C_SRAM_CORE.pin2, C_SRAM_CORE_IN.pin2, C_SRAM_MPU.pin2, C_SRAM_MPU_IN.pin2, C_VBB_MPU.pin2, C_VREF_CA.pin2, C_VREF_DQ.pin2, J_CARRIER.1, J_CARRIER.8, J_CARRIER.23, J_CARRIER.26, J_CARRIER.54, J_CARRIER.57, J_CARRIER.61, J_CARRIER.69, J_CARRIER.72, J_CARRIER.75, J_CARRIER.78, R_CPU_VREF_LOW.pin2, R_DDR_SW_EN.pin2, R_DDR_SW_OUT.pin2, R_DDR_VSEL.pin2, R_SYSBOOT3.pin1, R_SYSBOOT5.pin1, R_SYSBOOT6.pin1, R_SYSBOOT7.pin1, R_SYSBOOT8.pin1, R_SYSBOOT9.pin1, R_SYSBOOT10.pin1, R_SYSBOOT11.pin1, R_SYSBOOT12.pin1, R_SYSBOOT13.pin1, R_SYSBOOT15.pin1, R_VREF_LOW.pin2, R_VTP.pin2, R_ZQ.pin2, U1.A1, U1.A5, U1.A7, U1.A8, U1.A9, U1.A18, U1.B6, U1.B7, U1.B8, U1.B9, U1.C7, U1.C8, U1.C9, U1.D8, U1.E8, U1.F8, U1.G8, U1.G9, U1.G11, U1.G12, U1.H6, U1.H7, U1.H8, U1.H9, U1.H10, U1.H12, U1.J6, U1.J7, U1.J8, U1.J9, U1.J10, U1.J11, U1.K7, U1.K9, U1.K10, U1.K11, U1.L10, U1.L11, U1.L12, U1.L13, U1.M6, U1.M7, U1.M8, U1.M9, U1.M10, U1.M12, U1.M14, U1.N7, U1.N10, U1.N11, U1.N14, U1.V1, U1.V11, U1.V18, U_DDR.A9, U_DDR.B1, U_DDR.B3, U_DDR.B9, U_DDR.D1, U_DDR.D8, U_DDR.E1, U_DDR.E2, U_DDR.E8, U_DDR.F9, U_DDR.G1, U_DDR.G8, U_DDR.G9, U_DDR.J2, U_DDR.J8, U_DDR.M1, U_DDR.M9, U_DDR.P1, U_DDR.P9, U_DDR.T1, U_DDR.T9, U_DDR_SWITCH.EP, U_DDR_SWITCH.GND, U_PMIC.CC, U_PMIC.EP, Y_OSC0.pin2, Y_OSC0.pin4
JOY_L_CLICK: J_CARRIER.21, U1.V17
JOY_R_CLICK: J_CARRIER.22, U1.D18
J_SD_PIN1: J_CARRIER.6, U1.F18
LCD_D16: J_CARRIER.46, U1.U13
LCD_D17: J_CARRIER.47, U1.V13
LCD_D18: J_CARRIER.48, U1.R12
LCD_D19: J_CARRIER.49, U1.T12
LCD_D20: J_CARRIER.50, U1.U12
LCD_D21: J_CARRIER.51, U1.T11
LCD_D22: J_CARRIER.52, U1.T10
LCD_D23: J_CARRIER.53, U1.U10
LCD_DE: J_CARRIER.56, U1.R6
LCD_HSYNC: J_CARRIER.58, U1.R5
LCD_PCLK: J_CARRIER.55, U1.V5
LCD_RESET: J_CARRIER.60, U1.J18
LCD_VSYNC: J_CARRIER.59, U1.U5
LOCAL_BYPASS_C10: C_VBB_MPU.pin1, U1.C10
LOCAL_BYPASS_D9: C_SRAM_CORE.pin1, U1.D9
LOCAL_BYPASS_D11: C_SRAM_MPU.pin1, U1.D11
OSC0_BIAS_IN: C_OSC0_IN.pin1, R_OSC0_BIAS.pin1, U1.V10, Y_OSC0.pin1
OSC0_BIAS_OUT: R_OSC0_BIAS.pin2, R_OSC0_DRIVE.pin1, U1.U11
OSC0_OUT_LOAD: C_OSC0_OUT.pin1, R_OSC0_DRIVE.pin2, Y_OSC0.pin3
PMIC_BACKUP_SYSTEM: C_PMIC_SYS_BU.pin1, U_PMIC.SYS_BU
PMIC_I2C_SCL: R_PMIC_SCL.pin1, U1.C16, U_PMIC.SCL
PMIC_I2C_SDA: R_PMIC_SDA.pin1, U1.C17, U_PMIC.SDA
PMIC_INTERNAL_LDO: C_PMIC_INT_LDO.pin1, U_PMIC.INT_LDO
PMIC_IRQ: R_PMIC_IRQ.pin1, U1.T14, U_PMIC.nINT
POWER_KEY_BIAS: J_CARRIER.67, R_POWER_PB.pin1, U_PMIC.PB
RTC_POWER_HOLD: U1.C6, U_PMIC.PWR_EN
RTC_WAKE: R_PMIC_WAKE.pin1, U1.C5, U_PMIC.nWAKEUP
SD_DETECT: J_CARRIER.29, U1.C15
SYSBOOT0_SENSE: J_CARRIER.30, R_SYSBOOT0.pin2, U1.R1
SYSBOOT1_SENSE: J_CARRIER.31, R_SYSBOOT1.pin2, U1.R2
SYSBOOT2_SENSE: J_CARRIER.32, R_SYSBOOT2.pin2, U1.R3
SYSBOOT3_SENSE: J_CARRIER.33, R_SYSBOOT3.pin2, U1.R4
SYSBOOT4_SENSE: J_CARRIER.34, R_SYSBOOT4.pin2, U1.T1
SYSBOOT5_SENSE: J_CARRIER.35, R_SYSBOOT5.pin2, U1.T2
SYSBOOT6_SENSE: J_CARRIER.36, R_SYSBOOT6.pin2, U1.T3
SYSBOOT7_SENSE: J_CARRIER.37, R_SYSBOOT7.pin2, U1.T4
SYSBOOT8_SENSE: J_CARRIER.38, R_SYSBOOT8.pin2, U1.U1
SYSBOOT9_SENSE: J_CARRIER.39, R_SYSBOOT9.pin2, U1.U2
SYSBOOT10_SENSE: J_CARRIER.40, R_SYSBOOT10.pin2, U1.U3
SYSBOOT11_SENSE: J_CARRIER.41, R_SYSBOOT11.pin2, U1.U4
SYSBOOT12_SENSE: J_CARRIER.42, R_SYSBOOT12.pin2, U1.V2
SYSBOOT13_SENSE: J_CARRIER.43, R_SYSBOOT13.pin2, U1.V3
SYSBOOT14_SENSE: J_CARRIER.44, R_SYSBOOT14.pin2, U1.V4
SYSBOOT15_SENSE: J_CARRIER.45, R_SYSBOOT15.pin2, U1.T5
THROUGH_A: J_CARRIER.13, U1.V15
THROUGH_B: J_CARRIER.14, U1.M18
THROUGH_DN: J_CARRIER.10, U1.U16
THROUGH_LCD_BACKLIGHT_PWM: J_CARRIER.28, U1.C18
THROUGH_LFT: J_CARRIER.11, U1.U8
THROUGH_L_SHOULDER: J_CARRIER.19, U1.B17
THROUGH_RGT: J_CARRIER.12, U1.T13
THROUGH_R_SHOULDER: J_CARRIER.20, U1.B13
THROUGH_SD_CLK: J_CARRIER.2, U1.G17
THROUGH_SD_CMD: J_CARRIER.3, U1.G18
THROUGH_SD_CS: J_CARRIER.7, U1.F17
THROUGH_SD_DAT1_PULLUP: J_CARRIER.5, U1.G15
THROUGH_SD_MISO: J_CARRIER.4, U1.G16
THROUGH_SEL: J_CARRIER.17, U1.B12
THROUGH_STA: J_CARRIER.18, U1.U18
THROUGH_UP: J_CARRIER.9, U1.V12
THROUGH_USB_DM_A: J_CARRIER.25, U1.N18
THROUGH_USB_DP_A: J_CARRIER.24, U1.N17
THROUGH_X: J_CARRIER.15, U1.L18
THROUGH_Y: J_CARRIER.16, U1.K18
TOUCH_IRQ: J_CARRIER.64, U1.V14
TOUCH_SCL: J_CARRIER.63, U1.J15
TOUCH_SDA: J_CARRIER.62, U1.B16
USB0_VBUS_SENSE: J_CARRIER.80, U1.P15
VDDS_DDR: C_DDR1.pin1, C_DDR2.pin1, C_DDR3.pin1, C_DDR4.pin1, C_DDR5.pin1, C_DDR6.pin1, C_DDR7.pin1, C_DDR8.pin1, C_DDR9.pin1, C_DDR10.pin1, C_DDR11.pin1, C_DDR12.pin1, C_DDR33.pin1, C_DDR34.pin1, C_DDR37.pin1, C_DDR38.pin1, C_DDR39.pin1, C_DDR40.pin1, C_DDR_SW_IN.pin1, C_PMIC_DDR.pin1, L_PMIC_DDR.pin2, R_VREF_HIGH.pin2, U_DDR.A1, U_DDR.A8, U_DDR.B2, U_DDR.C1, U_DDR.C9, U_DDR.D2, U_DDR.D9, U_DDR.E9, U_DDR.F1, U_DDR.G7, U_DDR.H2, U_DDR.H9, U_DDR.K2, U_DDR.K8, U_DDR.N1, U_DDR.N9, U_DDR.R1, U_DDR.R9, U_DDR_SWITCH.VIN1, U_DDR_SWITCH.VIN2, U_PMIC.FB3, U_PMIC.IN_LS1
VDDS_DDR_CPU: C_DDR13.pin1, C_DDR14.pin1, C_DDR15.pin1, C_DDR16.pin1, C_DDR17.pin1, C_DDR18.pin1, C_DDR19.pin1, C_DDR20.pin1, C_DDR21.pin1, C_DDR22.pin1, C_DDR23.pin1, C_DDR24.pin1, C_DDR25.pin1, C_DDR26.pin1, C_DDR27.pin1, C_DDR28.pin1, C_DDR29.pin1, C_DDR30.pin1, C_DDR31.pin1, C_DDR32.pin1, C_DDR35.pin1, C_DDR36.pin1, C_DDR_SW_LOAD.pin1, R_CPU_VREF_HIGH.pin2, R_DDR_SW_OUT.pin1, U1.E5, U1.F5, U1.G5, U1.H5, U1.J5, U1.K5, U1.L5, U_DDR_SWITCH.VOUT1, U_DDR_SWITCH.VOUT2
VDDS_RTC_1V8: C_PMIC_RTC_IO.pin1, L_PMIC_RTC_IO.pin2, R_PMIC_WAKE.pin2, U1.B4, U1.D7, U_PMIC.FB6
VDD_CORE: C_PMIC_CORE.pin1, L_PMIC_CORE.pin2, U1.F6, U1.F7, U1.G6, U1.G7, U1.G10, U1.H11, U1.J12, U1.K6, U1.K8, U1.K12, U1.L6, U1.L7, U1.L8, U1.L9, U1.M11, U1.M13, U1.N8, U1.N9, U1.N12, U1.N13, U_PMIC.FB1
VDD_IO_3V3_SEQ: C_PMIC_IO_A.pin1, C_PMIC_IO_B.pin1, J_CARRIER.71, J_CARRIER.74, J_CARRIER.77, R_PMIC_IRQ.pin2, R_PMIC_POR.pin2, R_PMIC_SCL.pin2, R_PMIC_SDA.pin2, R_SYSBOOT0.pin1, R_SYSBOOT1.pin1, R_SYSBOOT2.pin1, R_SYSBOOT4.pin1, R_SYSBOOT14.pin1, U1.E10, U1.E11, U1.E12, U1.E13, U1.F14, U1.G14, U1.H14, U1.J14, U1.K14, U1.L14, U1.N5, U1.N15, U1.P5, U1.P6, U1.P7, U1.P8, U1.P10, U1.P11, U1.P12, U1.P13, U1.R15, U_PMIC.DCDC4
VDD_LDO1_1V8: C_PMIC_LDO1.pin1, C_SRAM_CORE_IN.pin1, C_SRAM_MPU_IN.pin1, U1.D10, U1.E6, U1.E7, U1.E9, U1.E14, U1.F9, U1.H15, U1.K13, U1.N6, U1.N16, U1.P9, U1.P14, U1.R10, U1.R11, U1.R16, U_PMIC.LDO1
VDD_MPU: C_MPU_HF1.pin1, C_MPU_HF2.pin1, C_MPU_HF3.pin1, C_MPU_HF4.pin1, C_MPU_HF5.pin1, C_MPU_LOCAL.pin1, C_PMIC_MPU.pin1, L_PMIC_MPU.pin2, U1.F10, U1.F11, U1.F12, U1.F13, U1.G13, U1.H13, U1.J13, U_PMIC.FB2
VDD_RTC_CORE_1V0: C_PMIC_RTC_CORE.pin1, L_PMIC_RTC_CORE.pin2, U1.D6, U_PMIC.FB5
VSYS_INTERNAL: C_DDR_SW_BIAS.pin1, C_PMIC_IN_BU.pin1, J_CARRIER.68, J_CARRIER.70, J_CARRIER.73, J_CARRIER.76, J_CARRIER.79, R_POWER_PB.pin2, U_DDR_SWITCH.VBIAS, U_PMIC.AC_DET, U_PMIC.IN_BIAS, U_PMIC.IN_BU, U_PMIC.IN_DCDC1, U_PMIC.IN_DCDC2, U_PMIC.IN_DCDC3, U_PMIC.IN_DCDC4, U_PMIC.IN_LDO1
channel_unnamedsubcircuitsubcircuit_source_group_1_connectivity_net71: R_DDR_VSEL.pin1, U_PMIC.DC34_SEL
channel_unnamedsubcircuitsubcircuit_source_group_1_connectivity_net74: L_PMIC_DDR.pin1, U_PMIC.L3
channel_unnamedsubcircuitsubcircuit_source_group_1_connectivity_net77: L_PMIC_RTC_CORE.pin1, U_PMIC.L5
channel_unnamedsubcircuitsubcircuit_source_group_1_connectivity_net79: L_PMIC_RTC_IO.pin1, U_PMIC.L6
channel_unnamedsubcircuitsubcircuit_source_group_1_connectivity_net83: U1.B5, U_PMIC.PGOOD_BU
channel_unnamedsubcircuitsubcircuit_source_group_1_connectivity_net85: L_PMIC_CORE.pin1, U_PMIC.L1
channel_unnamedsubcircuitsubcircuit_source_group_1_connectivity_net87: L_PMIC_MPU.pin1, U_PMIC.L2
channel_unnamedsubcircuitsubcircuit_source_group_1_connectivity_net97: C_DDR_SW_CT.pin1, U_DDR_SWITCH.CT
